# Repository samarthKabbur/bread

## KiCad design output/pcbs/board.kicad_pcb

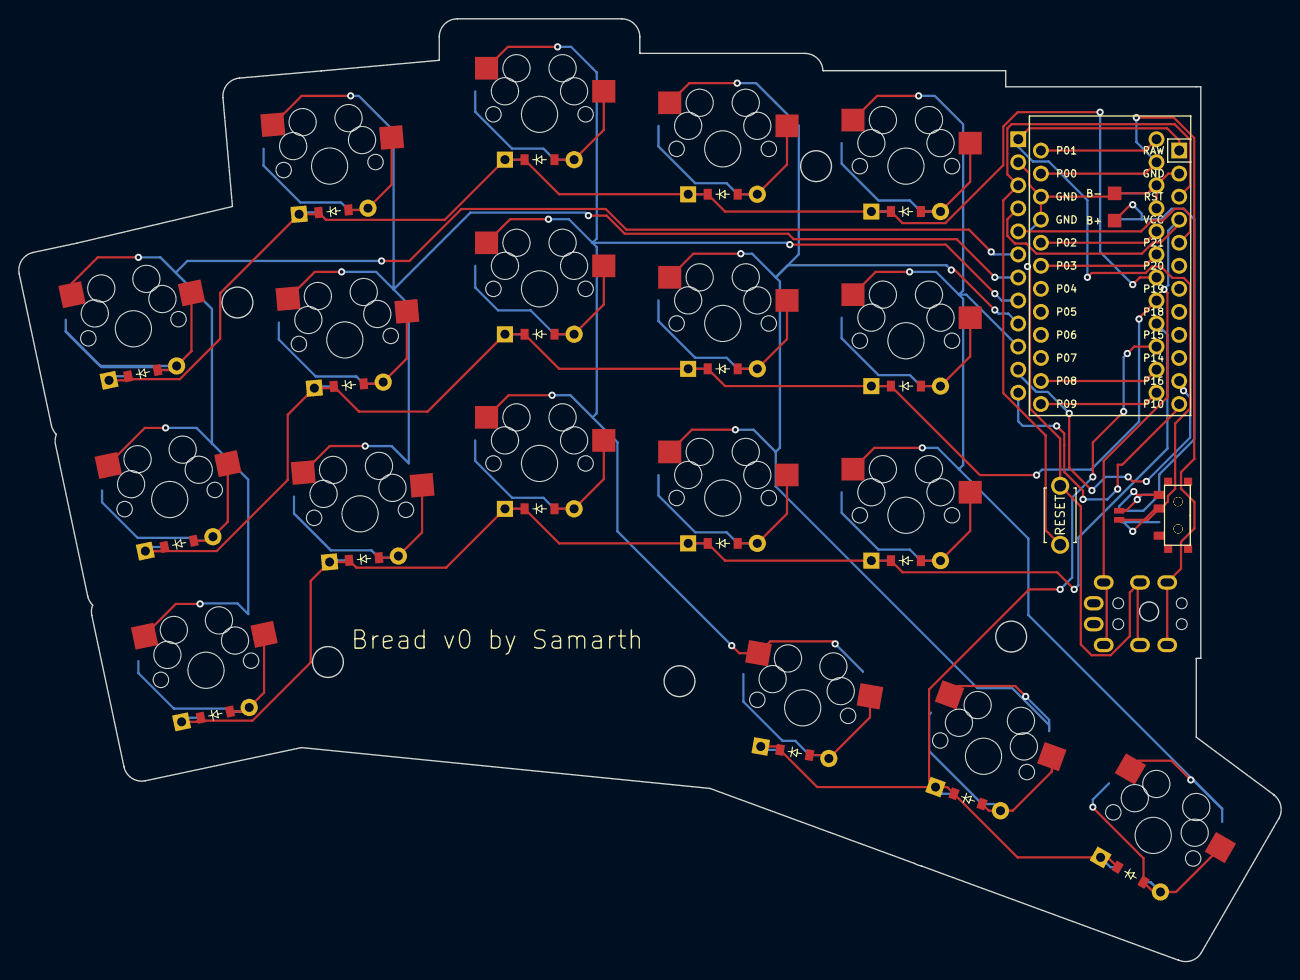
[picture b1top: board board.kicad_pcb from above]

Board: 2 copper layers, 139.1 x 103.9 mm, 46 parts (0 on the bottom side), 41 nets.

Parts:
B1: ResetSW
D1, D2, D3, D4, D5, D6, D7, D8, D9, D10, D11, D12, D13, D14, D15, D16, D17, D18: ComboDiode
J1, J2: Jumper
MCU1, MCU2: ProMicro
PAD1, PAD2: SMDPad
S1, S2, S3, S4, S5, S6, S7, S8, S9, S10, S11, S12, S13, S14, S15, S16, S17, S18: MX
T1, T2: SPDT_C128955
TRRS1: TRRS-PJ-320A-dual

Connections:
Bplus: J1.1, J2.1, PAD1.1, T1.3, T2.1
GND: B1.2, MCU1.2, MCU1.15, MCU1.16, MCU2.2, MCU2.15, MCU2.16, PAD2.1, TRRS1.3
P0: MCU1.14, MCU2.14, TRRS1.4
P1: MCU1.13, MCU2.13
P2: MCU1.17, MCU2.17
P3: MCU1.18, MCU2.18
P8: MCU1.23, MCU2.23
P9: MCU1.24, MCU2.24
P10: MCU1.12, MCU2.12
P16: MCU1.11, MCU2.11
P21: MCU1.5, MCU2.5
RAW: J1.2, J2.2, MCU1.1, MCU2.1, T1.2, T2.2
RST: B1.1, MCU1.3, MCU2.3
VCC: MCU1.4, MCU2.4, TRRS1.2
col_index: MCU1.9, S10.2, S11.2, S12.2, S17.2
col_inner: MCU1.10, S13.2, S14.2, S15.2, S18.2
col_middle: MCU1.8, S7.2, S8.2, S9.2, S16.2
col_pinky: MCU1.6, S1.2, S2.2, S3.2
col_ring: MCU1.7, S4.2, S5.2, S6.2
far_thumb: D18.2, S18.1
home_thumb: D17.2, S17.1
index_bottom: D10.2, S10.1
index_home: D11.2, S11.1
index_top: D12.2, S12.1
inner_bottom: D13.2, S13.1
inner_home: D14.2, S14.1
inner_top: D15.2, S15.1
middle_bottom: D7.2, S7.1
middle_home: D8.2, S8.1
middle_top: D9.2, S9.1
near_thumb: D16.2, S16.1
pinky_bottom: D1.2, S1.1
pinky_home: D2.2, S2.1
pinky_top: D3.2, S3.1
ring_bottom: D4.2, S4.1
ring_home: D5.2, S5.1
ring_top: D6.2, S6.1
row_bottom: D1.1, D4.1, D7.1, D10.1, D13.1, MCU1.21
row_home: D2.1, D5.1, D8.1, D11.1, D14.1, MCU1.20
row_thumb: D16.1, D17.1, D18.1, MCU1.22
row_top: D3.1, D6.1, D9.1, D12.1, D15.1, MCU1.19

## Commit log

2025-11-16 bread(key)board
2025-11-16 completed routing
2025-11-17 enlarging edge cuts layer
